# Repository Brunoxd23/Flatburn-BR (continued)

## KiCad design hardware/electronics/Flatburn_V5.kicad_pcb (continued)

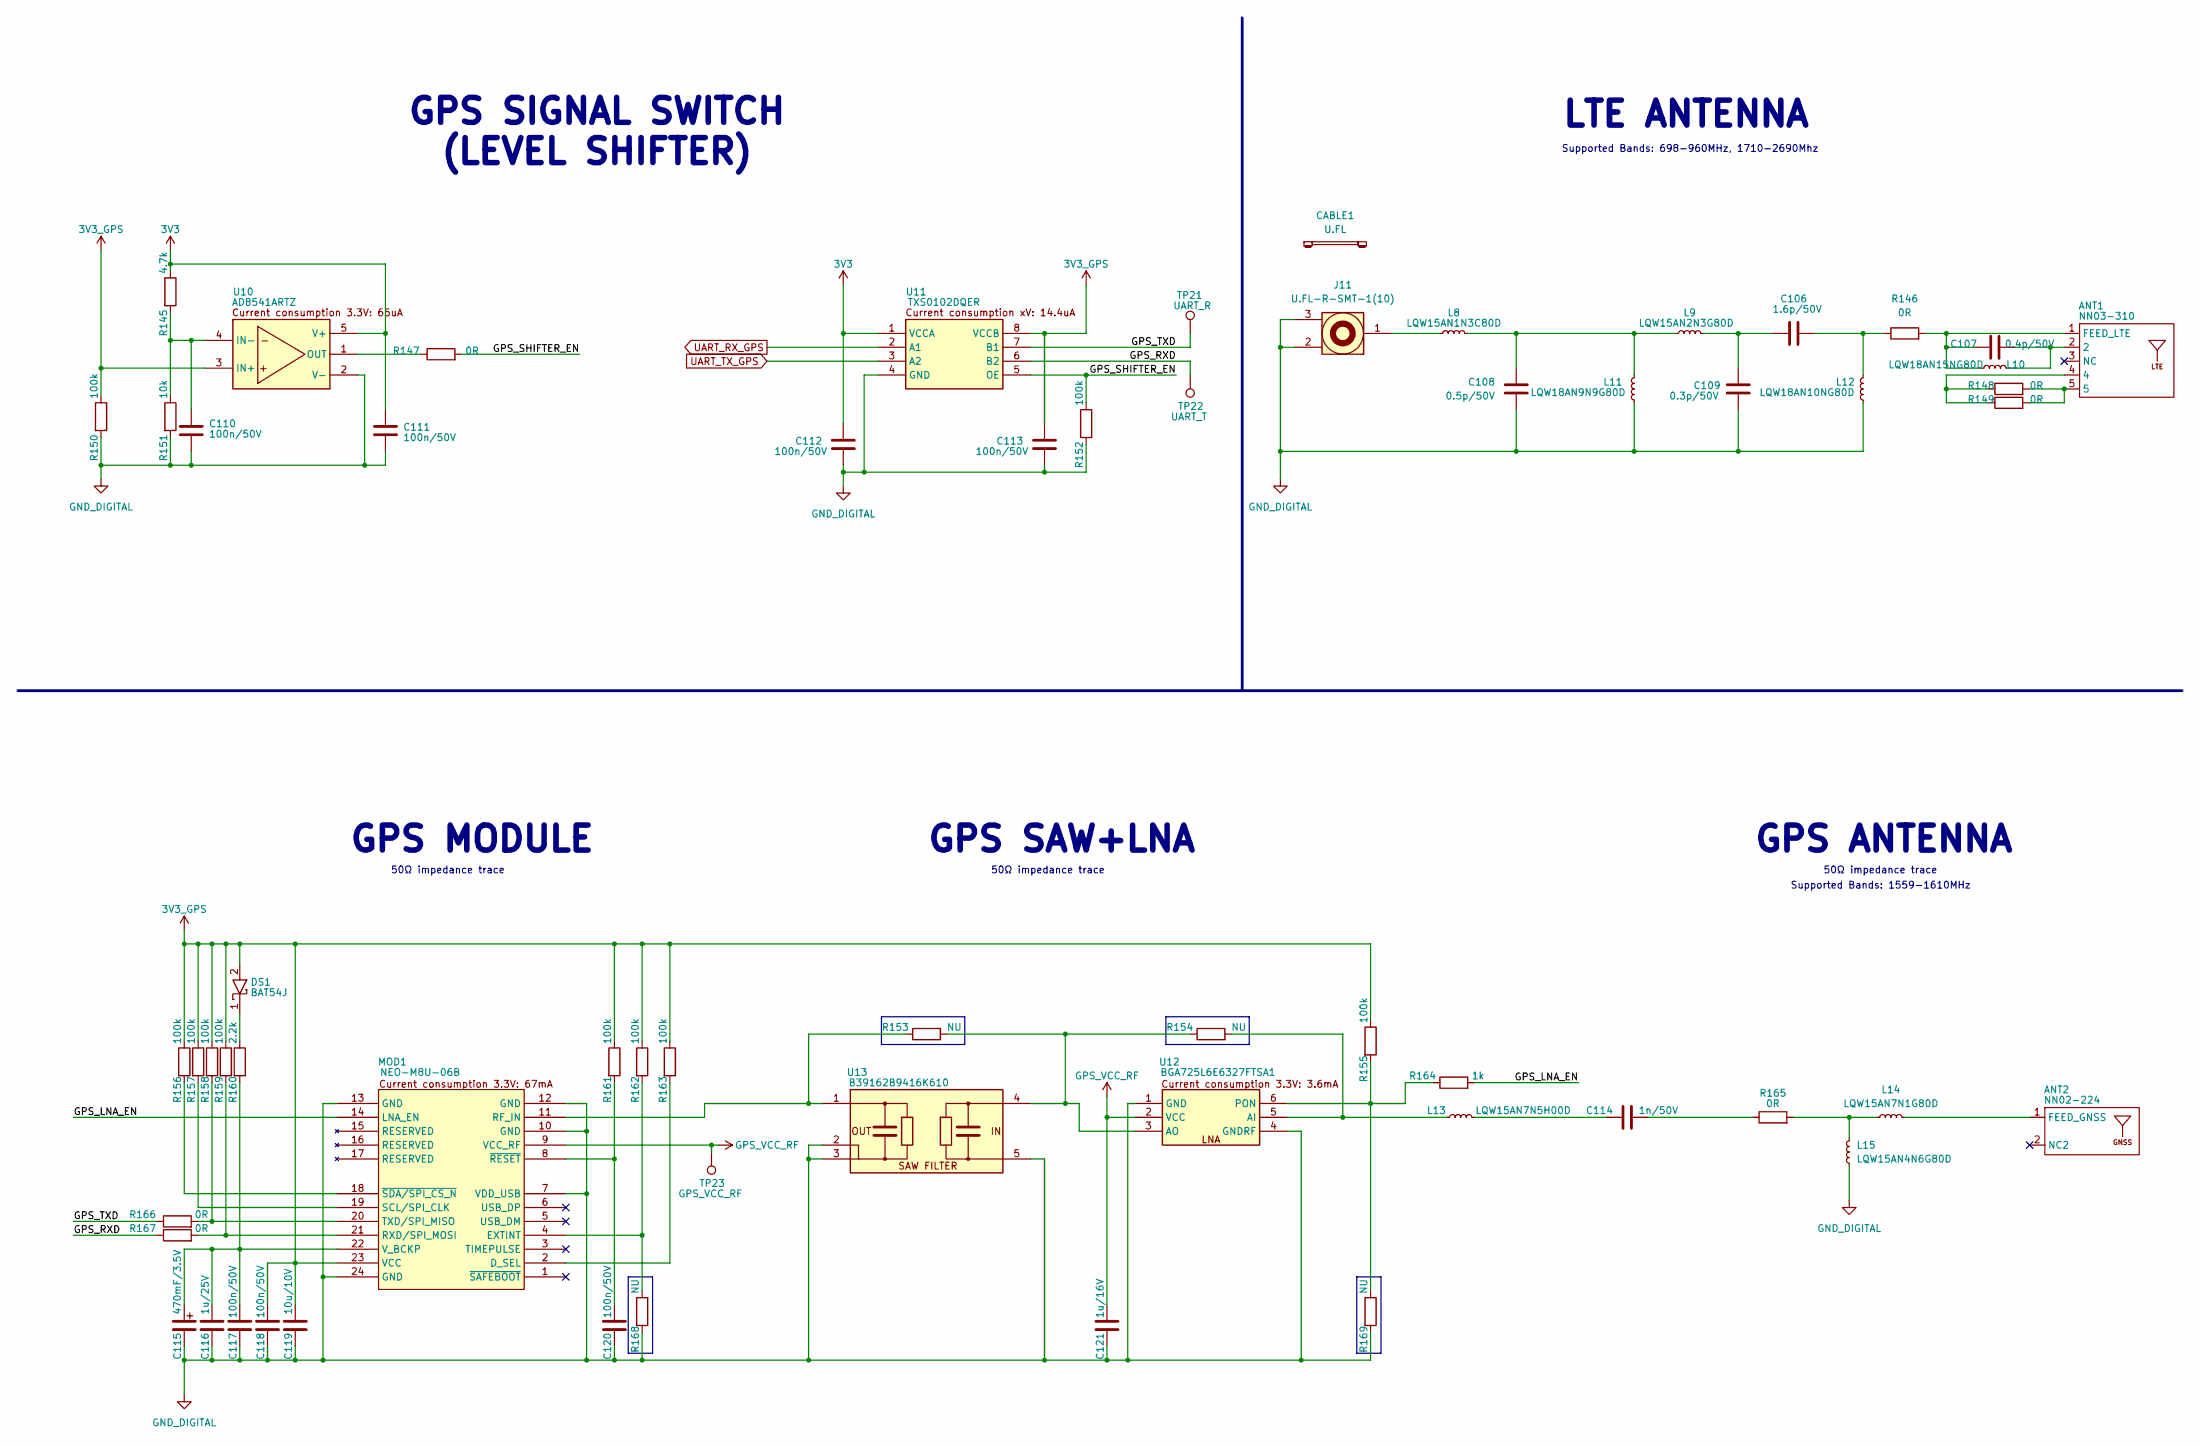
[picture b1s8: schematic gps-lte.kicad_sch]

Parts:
ANT1: NN03-310; XCVR_NN03-310; MPN NN03-310
ANT2: NN02-224; XCVR_NN02-224; MPN NN02-224
C106: 1.6p/50V; C_0402_1005Metric; MPN GJM1555C1H1R6WB01D
C107: 0.4p/50V; C_0402_1005Metric; MPN GJM1555C1HR40WB01D
C108: 0.5p/50V; C_0402_1005Metric; MPN GJM1555C1HR50WB01D
C109: 0.3p/50V; C_0402_1005Metric; MPN GJM1555C1HR30WB01D
C110, C111, C112, C113, C117, C118, C120: 100n/50V; C_0402_1005Metric
C114: 1n/50V; C_0402_1005Metric
C115: 470mF/3.5V; FCS0V474ZFTBR24_KEM; MPN FCS0V474ZFTBR24
C116: 1u/25V; C_0603_1608Metric; MPN CL10B105KA8NNNC
C119: 10u/10V; C_0603_1608Metric
C121: 1u/16V; C_0402_1005Metric; MPN GRM155C71C105KE11D
CABLE1: U.FL; MPN 2016493-1
DS1: BAT54J; D_SOD-323F; MPN BAT54J,115
J11: U.FL-R-SMT-1(10); MPN U.FL-R-SMT-1(10)
L8: LQW15AN1N3C80D; LQW15AN4N1G80D; MPN LQW15AN1N3C80D
L9: LQW15AN2N3G80D; MPN LQW15AN2N3G80D
L10: LQW18AN15NG80D; LQW18AN7N2G80D; MPN LQW18AN15NG80D
L11: LQW18AN9N9G80D; LQW18AN7N2G80D; MPN LQW18AN9N9G80D
L12: LQW18AN10NG80D; LQW18AN7N2G80D; MPN LQW18AN10NG80D
L13: LQW15AN7N5H00D; MPN LQW15AN7N5H00D
L14: LQW15AN7N1G80D; LQW15AN4N1G80D; MPN LQW15AN7N1G80D
L15: LQW15AN4N6G80D; LQW15AN4N1G80D; MPN LQW15AN4N6G80D
MOD1: NEO-M8U-06B; MOD24_NEO-M8U_UBL; MPN NEO-M8U-06B
R145: 4.7k; R_0402_1005Metric
R146, R148, R149, R165, R166, R167: 0R; R_0402_1005Metric; MPN MCS04020Z0000ZE000
R147: 0R; R_0402_1005Metric; MPN RCS04020000Z0ED
R150, R152, R155, R156, R157, R158, R159, R161, R162, R163: 100k; R_0402_1005Metric
R151: 10k; R_0402_1005Metric
R153, R154: NU; R_0402_1005Metric; MPN RCS04020000Z0ED
R160: 2.2k; R_0402_1005Metric
R164: 1k; R_0402_1005Metric
R168, R169: NU; R_0402_1005Metric
TP21: UART_R; TestPoint_Pad_D1.0mm
TP22: UART_T; TestPoint_Pad_D1.0mm
TP23: GPS_VCC_RF; TestPoint_Pad_D1.0mm
U10: AD8541ARTZ; SOT-23-5; MPN TXS0102DQER
U11: TXS0102DQER; SON35P100X140X40-8N; MPN TXS0102DQER
U12: BGA725L6E6327FTSA1; BGS12SN6E6327XTSA1; MPN BGA725L6E6327FTSA1
U13: B39162B9416K610; MPN B39162B9416K610

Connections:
3V3: C111.1, C112.1, R145.1, U10.5 (V+), U11.1 (VCCA); also elsewhere on the board
3V3_GPS: C113.1, C118.1, C119.1, DS1.2, MOD1.23 (VCC), R150.1, R155.1, R156.1, R157.1, R158.1, R159.1, R161.1, R162.1, R163.1, U10.3 (IN+), U11.8 (VCCB); also elsewhere on the board
/06 - GPS-LTE/GPS_LNA_EN: MOD1.14 (LNA_EN), R164.2
/06 - GPS-LTE/GPS_RXD: R167.1, TP22.1, U11.6 (B2)
/06 - GPS-LTE/GPS_SHIFTER_EN: R147.2, R152.1, U11.5 (OE)
/06 - GPS-LTE/GPS_TXD: R166.1, TP21.1, U11.7 (B1)
GND_DIGITAL: C108.2, C109.2, C110.2, C111.2, C112.2, C113.2, C115.2 (-), C116.2, C117.2, C118.2, C119.2, C120.2, C121.2, J11.2, J11.3, L11.2, L12.2, L15.2, MOD1.7 (VDD_USB), MOD1.10 (GND), MOD1.12 (GND), MOD1.13 (GND), MOD1.24 (GND), R150.2, R151.2, R152.2, R168.2, R169.2, U10.2 (V-), U11.4 (GND), U12.1 (GND), U12.4 (GNDRF), U13.2 (GND1), U13.3 (GND2), U13.5 (GND3); also elsewhere on the board
GPS_VCC_RF: C121.1, MOD1.9 (VCC_RF), TP23.1, U12.2 (VCC)
unnamed: ANT1.1 (FEED_LTE), C107.1, L10.2, R146.2
unnamed: ANT1.2, C107.2, L10.1
unnamed: ANT1.4, R148.1, R149.1
unnamed: ANT1.5, R148.2, R149.2
unnamed: ANT2.1 (FEED_GNSS), L14.1
unnamed: C106.1, C109.1, L9.1
unnamed: C106.2, L12.1, R146.1
unnamed: C108.1, L8.1, L9.2, L11.1
unnamed: C114.1, L13.1
unnamed: C114.2, R165.1
unnamed: C115.1 (+), C116.1, C117.1, MOD1.22 (V_BCKP), R160.2
unnamed: DS1.1, R160.1
unnamed: J11.1, L8.2
unnamed: L14.2, L15.1, R165.2
unnamed: MOD1.2 (D_SEL), R163.2
unnamed: MOD1.4 (EXTINT), R162.2, R168.1
unnamed: MOD1.11 (RF_IN), R153.1, U13.1 (OUT)
unnamed: MOD1.21 (RXD/SPI_MOSI), R159.2, R167.2
unnamed: MOD1.19 (SCL/SPI_CLK), R157.2
unnamed: MOD1.20 (TXD/SPI_MISO), R158.2, R166.2
unnamed: C120.1, MOD1.8 (~RESET), R161.2
unnamed: MOD1.18 (~SDA/SPI_CS_N), R156.2
unnamed: C110.1, R145.2, R151.1, U10.4 (IN-)
unnamed: R147.1, U10.1 (OUT)
unnamed: L13.2, R154.2, U12.5 (AI)
unnamed: R153.2, R154.1, U12.3 (AO), U13.4 (IN)
unnamed: R155.2, R164.1, R169.1, U12.6 (PON)
UART_RX_GPS: U11.2 (A1); also elsewhere on the board
UART_TX_GPS: U11.3 (A2); also elsewhere on the board

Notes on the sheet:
GPS SIGNAL SWITCH (LEVEL SHIFTER)
GPS SAW+LNA
GPS ANTENNA
50Ω impedance trace
LTE ANTENNA
GPS MODULE
Supported Bands: 698-960MHz, 1710-2690Mhz
Supported Bands: 1559-1610MHz

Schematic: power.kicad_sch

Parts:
C5, C6, C14: 10n/50V; C_0402_1005Metric
C7: 4.7u/35V; C_0603_1608Metric
C8, C11: 10u/10V; C_0603_1608Metric
C9, C10: 330p/10V; C_0402_1005Metric; MPN C0402C331K8RACTU
C12, C21: 4.7u/10V; C_0603_1608Metric
C13: 47u/50V; CP_Elec_8x10; MPN GXC1H470MCQ1GS
C15, C16: 47n/25V; C_0402_1005Metric
C17, C18, C24, C25, C26: 10u/50V; C_0805_2012Metric; MPN GRM21BR61H106KE43L
C19, C27, C33: 100n/50V; C_0402_1005Metric
C20: 1n/50V; C_0402_1005Metric
C22, C23: 10u/25V; C_0603_1608Metric
C28, C29, C30, C31, C32: 10u/25V; C_0603_1608Metric; MPN GRM188R61E106KA73D
DZ2, DZ3: BZT52C12T-7; D_SOD-523; MPN BZT52C12T-7
J8: STRIP-2P-M; PinHeader_1x02_P2.54mm_Vertical
L3: SPM6550T-1R0M100A; SPM6550; MPN SPM6550T-1R0M100A
LD1: IN-S63ASR; INS63ASR; MPN IN-S63ASR
PB1: 1571634-2; 15716342; MPN 1571634-2
Q2, Q3, Q4, Q5: SISH402DN-T1-GE3; PowerPAK 121-8; MPN SISH402DN-T1-GE3
Q6: BSS84WQ-7-F; SOT-323_SC-70; MPN BSS84WQ-7-F
R5: NU; R_1206_3216Metric; MPN RCA12060000ZSEA
R6, R7, R9, R11, R13, R15, R17, R18, R19, R24, R29, R33: 10k; R_0402_1005Metric
R8, R10, R12, R14, R16: NU; R_0402_1005Metric
R20, R25: 264R; R_0603_1608Metric; MPN CRCW0603294RFKEA
R21: 255k; R_0402_1005Metric; MPN RC0402FR-07255KL
R22: 100k; R_0402_1005Metric
R23: 560R; R_0402_1005Metric
R26: NU; R_0603_1608Metric; MPN RCA06030000ZSEA
R27: NU; R_0402_1005Metric; MPN RCS04020000Z0ED
R28, R31: 100R; R_0402_1005Metric
R30: 5.23k; R_0402_1005Metric
R32: 30.1k; R_0402_1005Metric
R34: NU; R_0603_1608Metric
R35: 3k; R_0603_1608Metric
TP1: TestPoint; TestPoint_Pad_D1.0mm
TP2: CAP_MIS; TestPoint_Pad_D1.0mm
TP3: n_SINK_EN; TestPoint_Pad_D1.0mm
TP4: VSOLAR; TestPoint_Pad_D1.0mm
TP5: VSYS; TestPoint_Pad_D1.0mm
TP6: VBUS; TestPoint_Pad_D1.0mm
TP7: BC_LDO; TestPoint_Pad_D1.0mm
TP8: VUSB_PD; TestPoint_Pad_D1.0mm
TP9: VBAT; TestPoint_Pad_D1.0mm
TP10: GND; TestPoint_Pad_D1.0mm
TP37: n_FAULT_IN; TestPoint_Pad_D1.0mm
TVS19: D5V0S1U2LP-7B; D5V0S1U2LP7B; MPN M-621-D5V0S1U2LP-7B
U1: TPS25730DREFR; MPN TPS25730DREFR
U2: BQ25798RQMR; MPN BQ25798RQMR

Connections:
/03 - POWER/ADCIN1: R8.1, R13.2, U1.2 (ADCIN1)
/03 - POWER/ADCIN2: R9.1, R14.2, U1.3 (ADCIN2)
/03 - POWER/ADCIN3: R10.1, R15.2, U1.5 (ADCIN3)
/03 - POWER/ADCIN4: R11.1, R16.2, U1.7 (ADCIN4)
/03 - POWER/ILIM_HIZ: R21.2, R22.1, U2.17 (ILIM_HIZ)
/03 - POWER/REGN: C21.1, R21.1, R23.1, R24.1, R29.1, R30.1, TP7.1, U2.5 (REGN)
/03 - POWER/STAT: Q6.1 (G), R24.2, R27.1, U2.1 (STAT)
/03 - POWER/TS: J8.1, R30.2, R32.1, R33.1, U2.16 (TS)
/03 - POWER/VUSB_PD: C13.1, C14.1, Q4.5 (D), Q4.6 (D), Q4.7 (D), Q4.8 (D), Q4.9 (D), R5.2, TP1.1, TP8.1, U1.20 (PPHV_1), U1.21 (PPHV_2), U1.22 (PPHV_3), U1.41 (PPHV_4), U2.8 (VAC2)
CC1: C9.1, U1.28 (CC1); also elsewhere on the board
CC2: C10.1, U1.29 (CC2); also elsewhere on the board
GND_DIGITAL: C5.2, C6.2, C7.2, C8.2, C9.2, C10.2, C11.2, C12.2, C13.2, C14.2, C17.2, C18.2, C19.2, C20.2, C21.2, C22.2, C23.2, C24.2, C25.2, C26.2, C27.2, C28.2, C29.2, C30.2, C31.2, C32.2, C33.2, J8.2, PB1.3, PB1.4, Q6.3 (D), R13.1, R14.1, R15.1, R16.1, R17.2, R18.2, R19.2, R22.2, R32.2, R33.2, R34.2, R35.2, TP10.1, TVS19.2, U1.11 (GND_1), U1.12 (GND_2), U1.14 (GND_3), U1.16 (GND_4), U1.17 (GND_5), U1.31 (GND_6), U1.34 (GND_7), U1.35 (GND_8), U1.39 (GND_9), U1.44 (GND_10), U2.13 (~CE), U2.27 (GND); also elsewhere on the board
I2C_SCL: U1.9 (I2CT_SCL), U2.14 (SCL); also elsewhere on the board
I2C_SDA: U1.8 (I2CT_SDA), U2.15 (SDA); also elsewhere on the board
LDO_3V3: C11.1, R6.1, R7.1, R8.2, R9.2, R10.2, R11.2, R12.1, U1.1 (LDO_3V3)
unnamed: DZ2.2, Q2.1 (S), Q2.2 (S), Q2.3 (S), Q3.1 (S), Q3.2 (S), Q3.3 (S)
unnamed: DZ3.2, Q4.1 (S), Q4.2 (S), Q4.3 (S), Q5.1 (S), Q5.2 (S), Q5.3 (S)
unnamed: LD1.2 (A), R23.2
unnamed: LD1.1 (K), Q6.2 (S), R27.2
unnamed: PB1.1, PB1.2, R31.1, TVS19.1
unnamed: DZ2.1, Q2.4 (G), Q3.4 (G), R20.1
unnamed: DZ3.1, Q4.4 (G), Q5.4 (G), R25.1
unnamed: R6.2, TP2.1, U1.6 (CAP_MIS)
unnamed: U1.15 (DRAIN_1), U1.30 (DRAIN_2), U1.40 (DRAIN_3)
unnamed: C12.1, U1.4 (LDO_1V5)
unnamed: R19.1, U1.26 (RESERVED_1)
unnamed: R18.1, U1.27 (RESERVED_2)
unnamed: R17.1, U1.36 (RESERVED_3)
unnamed: C8.1, U1.38 (VIN_3V3)
unnamed: R7.2, TP37.1, U1.18 (~FAULT_IN)
unnamed: R20.2, U2.11 (ACDRV1)
unnamed: R25.2, U2.10 (ACDRV2)
unnamed: R28.1, U2.18 (BATP)
unnamed: C15.1, U2.4 (BTST1)
unnamed: C16.2, U2.19 (BTST2)
unnamed: C24.1, C25.1, C26.1, C27.1, U2.29 (PMID)
unnamed: R34.1, R35.1, U2.20 (PROG)
unnamed: C20.1, U2.24 (SDRV)
unnamed: C15.2, L3.1, U2.28 (SW1)
unnamed: C16.1, L3.2, U2.26 (SW2)
unnamed: R29.2, U2.21 (~INT)
unnamed: R31.2, U2.12 (~QON)
VBAT: C22.1, C23.1, R26.1, R28.2, TP9.1, U2.22 (BAT), U2.23 (BAT); also elsewhere on the board
VBUS: Q3.5 (D), Q3.6 (D), Q3.7 (D), Q3.8 (D), Q3.9 (D), Q5.5 (D), Q5.6 (D), Q5.7 (D), Q5.8 (D), Q5.9 (D); also elsewhere on the board
VBUS_CURSEN: C17.1, C18.1, C19.1, TP6.1, U2.2 (VBUS), U2.3 (VBUS); also elsewhere on the board
VSOLAR: Q2.5 (D), Q2.6 (D), Q2.7 (D), Q2.8 (D), Q2.9 (D), TP4.1, U2.9 (VAC1); also elsewhere on the board
VSYS: C28.1, C29.1, C30.1, C31.1, C32.1, C33.1, R26.2, TP5.1, U2.25 (SYS); also elsewhere on the board
VUSB: C5.1, C6.1, C7.1, R5.1, U1.23 (VBUS_IN_1), U1.24 (VBUS_IN_2), U1.25 (VBUS_IN_3), U1.32 (VBUS_1), U1.33 (VBUS_2), U1.42 (VBUS_IN_4), U1.43 (VBUS_3); also elsewhere on the board
nUSB_SINK_EN: R12.2, TP3.1, U1.19 (~SINK_EN); also elsewhere on the board

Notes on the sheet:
ADCINx pins Configure Default Behavior,read Datasheet for more info In this version: 5V min 20V max 0,5A min 5A max I2C Address: 0x20
CURRENT SENSE VBUS
PROG pin sets default Switching Frequency and Battery Cell Count In this version: f:1.5MHz Cell:1S
I2C Address: 0x6B
Bypass U1
External battery thermistor connector If thermistor is mounted, remove R33 10K resistor
BATTERY CHARGER
Battery charger reset 10s press
VSYSMax 1S Battery = 4.55V VSYSMax 2S Battery = 8.77V
Input current limit Set to 500mA To increase change IINDPM register value
LED ON = Charging in progress LED BLINK = Fault condition LED OFF = Charging completed/disabled
I2C Address: 0x20
USB PD CONTROLLER

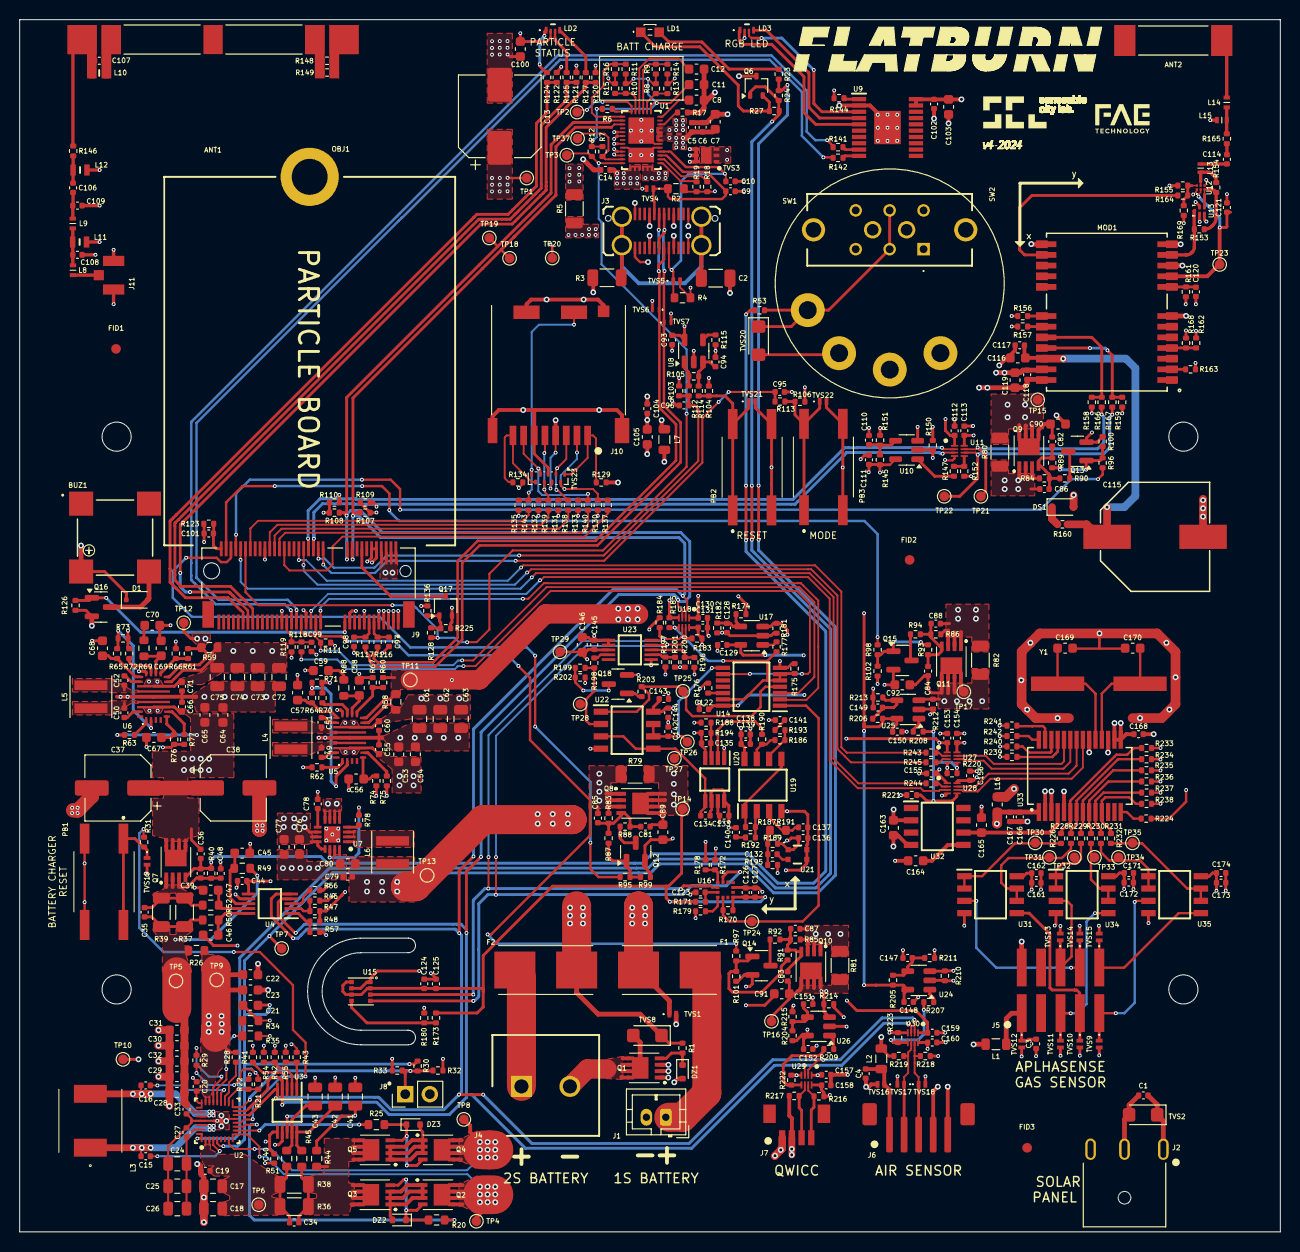
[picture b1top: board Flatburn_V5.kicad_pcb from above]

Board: 4 copper layers, 130.0 x 125.0 mm, 586 parts (0 on the bottom side), 290 nets.

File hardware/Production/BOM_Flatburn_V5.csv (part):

Item,Reference,Value,MPN,Description,Distributor,Pkg Type,Footprint,Notes
1,ANT1,NN03-310,NN03-310,"Ignion TRIO mXTENDT (NN03-310),GSM, UMTS, LTE, LTE-M, NB-IoT, 5G, GNSS, Bluetooth, 400-8000MHz, 30X3X1mm",M-128-NN03-310 ,SMD,FAE-ANT:XCVR_NN03-310,
2,ANT2,NN02-224,NN02-224 ,"Ignion RUN mXTENDâ„¢ (NN02-224) GNSS antenna, 824-8000 MHz",M-128-NN02-224 ,SMD,FAE-ANT:XCVR_NN02-224,
3,BUZ1,ST-025BH,ST-025BH,"BUZZER MAGN 3V 7.5X7.5 SMD, 2,7KHz, 8RdBA",D-433-1087-2-ND,SMD,FAE-BUZZ:ST-025BH_SOB,
4,C1,100n/50V,,CHIP CAP.CER. 100nF 50V 10% X7R 0402,FAE-043362,SMD,Capacitor_SMD:C_0402_1005Metric,
5,C2,10n/1kV,,CHIP CAP.CER. 10nF 1kV 10% X7R 1206,FAE-028470,SMD,Capacitor_SMD:C_1206_3216Metric,
6,C3,100n/50V,,CHIP CAP.CER. 100nF 50V 10% X7R 0402,FAE-043362,SMD,Capacitor_SMD:C_0402_1005Metric,
7,C4,100n/50V,,CHIP CAP.CER. 100nF 50V 10% X7R 0402,FAE-043362,SMD,Capacitor_SMD:C_0402_1005Metric,
8,C5,10n/50V,,CHIP CAP.CER. 10nF 50V 10% X7R 0402,FAE-101362,SMD,Capacitor_SMD:C_0402_1005Metric,
9,C6,10n/50V,,CHIP CAP.CER. 10nF 50V 10% X7R 0402,FAE-101362,SMD,Capacitor_SMD:C_0402_1005Metric,
10,C7,4.7u/35V,,CHIP CAP.CER. 4.7u 35V 10% X5R 0603,FAE-057733,SMD,Capacitor_SMD:C_0603_1608Metric,
11,C8,10u/10V,,CHIP CAP.CER. 10u 10V 10% X5R 0603,FAE-028168,SMD,Capacitor_SMD:C_0603_1608Metric,
12,C9,330p/10V,C0402C331K8RACTU,CHIP CAP.CER. 330p 10V 10% X7R 0402,M-80-C0402C331K8R ,SMD,Capacitor_SMD:C_0402_1005Metric,
13,C10,330p/10V,C0402C331K8RACTU,CHIP CAP.CER. 330p 10V 10% X7R 0402,M-80-C0402C331K8R ,SMD,Capacitor_SMD:C_0402_1005Metric,
14,C11,10u/10V,,CHIP CAP.CER. 10u 10V 10% X5R 0603,FAE-028168,SMD,Capacitor_SMD:C_0603_1608Metric,
15,C12,4.7u/10V,,CHIP CAP.CER. 4.7u 10V 10% X5R 0603,FAE-033362,SMD,Capacitor_SMD:C_0603_1608Metric,
16,C13,47u/50V,GXC1H470MCQ1GS,AL ORG POLR. 47u 50V 20% 8X10,M-647-GXC1H470MCQ1GS ,SMD,Capacitor_SMD:CP_Elec_8x10,
17,C14,10n/50V,,CHIP CAP.CER. 10nF 50V 10% X7R 0402,FAE-101362,SMD,Capacitor_SMD:C_0402_1005Metric,
18,C15,47n/25V,,CHIP CAP.CER. 47nF 25V 10% X7R 0402,FAE-029703,SMD,Capacitor_SMD:C_0402_1005Metric,
19,C16,47n/25V,,CHIP CAP.CER. 47nF 25V 10% X7R 0402,FAE-029703,SMD,Capacitor_SMD:C_0402_1005Metric,
20,C17,10u/50V,GRM21BR61H106KE43L,CHIP CAP.CER. 10u 50V 10% X5R 0805,M-81-GRM21BR61H106KE3L ,SMD,Capacitor_SMD:C_0805_2012Metric,
21,C18,10u/50V,GRM21BR61H106KE43L,CHIP CAP.CER. 10u 50V 10% X5R 0805,M-81-GRM21BR61H106KE3L ,SMD,Capacitor_SMD:C_0805_2012Metric,
22,C19,100n/50V,,CHIP CAP.CER. 100nF 50V 10% X7R 0402,FAE-043362,SMD,Capacitor_SMD:C_0402_1005Metric,
23,C20,1n/50V,,CHIP CAP.CER. 1nF 50V 10% X7R 0402,FAE-043572,SMD,Capacitor_SMD:C_0402_1005Metric,
24,C21,4.7u/10V,,CHIP CAP.CER. 4.7u 10V 10% X5R 0603,FAE-033362,SMD,Capacitor_SMD:C_0603_1608Metric,
25,C22,10u/25V,,CHIP CAP.CER. 10u 25V 20% X5R 0603,FAE-055937,SMD,Capacitor_SMD:C_0603_1608Metric,
26,C23,10u/25V,,CHIP CAP.CER. 10u 25V 20% X5R 0603,FAE-055937,SMD,Capacitor_SMD:C_0603_1608Metric,
27,C24,10u/50V,GRM21BR61H106KE43L,CHIP CAP.CER. 10u 50V 10% X5R 0805,M-81-GRM21BR61H106KE3L ,SMD,Capacitor_SMD:C_0805_2012Metric,
28,C25,10u/50V,GRM21BR61H106KE43L,CHIP CAP.CER. 10u 50V 10% X5R 0805,M-81-GRM21BR61H106KE3L ,SMD,Capacitor_SMD:C_0805_2012Metric,
29,C26,10u/50V,GRM21BR61H106KE43L,CHIP CAP.CER. 10u 50V 10% X5R 0805,M-81-GRM21BR61H106KE3L ,SMD,Capacitor_SMD:C_0805_2012Metric,
30,C27,100n/50V,,CHIP CAP.CER. 100nF 50V 10% X7R 0402,FAE-043362,SMD,Capacitor_SMD:C_0402_1005Metric,
31,C28,10u/25V,GRM188R61E106KA73D,CHIP CAP.CER. 10u 25V 10% X5R 0603,M-81-GRM188R61E106KA3D ,SMD,Capacitor_SMD:C_0603_1608Metric,
32,C29,10u/25V,GRM188R61E106KA73D,CHIP CAP.CER. 10u 25V 10% X5R 0603,M-81-GRM188R61E106KA3D ,SMD,Capacitor_SMD:C_0603_1608Metric,
33,C30,10u/25V,GRM188R61E106KA73D,CHIP CAP.CER. 10u 25V 10% X5R 0603,M-81-GRM188R61E106KA3D ,SMD,Capacitor_SMD:C_0603_1608Metric,
34,C31,10u/25V,GRM188R61E106KA73D,CHIP CAP.CER. 10u 25V 10% X5R 0603,M-81-GRM188R61E106KA3D ,SMD,Capacitor_SMD:C_0603_1608Metric,
35,C32,10u/25V,GRM188R61E106KA73D,CHIP CAP.CER. 10u 25V 10% X5R 0603,M-81-GRM188R61E106KA3D ,SMD,Capacitor_SMD:C_0603_1608Metric,
36,C33,100n/50V,,CHIP CAP.CER. 100nF 50V 10% X7R 0402,FAE-043362,SMD,Capacitor_SMD:C_0402_1005Metric,
37,C34,100n/50V,,CHIP CAP.CER. 100nF 50V 10% X7R 0402,FAE-043362,SMD,Capacitor_SMD:C_0402_1005Metric,
38,C35,100n/50V,,CHIP CAP.CER. 100nF 50V 10% X7R 0402,FAE-043362,SMD,Capacitor_SMD:C_0402_1005Metric,
39,C36,10p/50V,GCM1555C1H100JA16D,CHIP CAP.CER. 10p 50V 5% C0G 0402,FAE-043366,SMD,Capacitor_SMD:C_0402_1005Metric,
40,C37,220u/25V,UCM1E221MCL1GS,"EL POLR. 220u 25V 20% 6,3x7,7",M-647-UCM1E221MCL1GS ,SMD,Capacitor_SMD:CP_Elec_6.3x7.7,
41,C38,220u/25V,UCM1E221MCL1GS,"EL POLR. 220u 25V 20% 6,3x7,7",M-647-UCM1E221MCL1GS ,SMD,Capacitor_SMD:CP_Elec_6.3x7.7,
42,C39,NU,,CHIP CAP.CER. 100nF 50V 10% X7R 0402,FAE-043362,SMD,Capacitor_SMD:C_0402_1005Metric,NOT MOUNTED
43,C40,100n/50V,,CHIP CAP.CER. 100nF 50V 10% X7R 0402,FAE-043362,SMD,Capacitor_SMD:C_0402_1005Metric,
44,C41,1u/50V,,CHIP CAP.CER. 1u 50V 10% X7R 0805,FAE-027166,SMD,Capacitor_SMD:C_0805_2012Metric,
45,C42,1u/50V,,CHIP CAP.CER. 1u 50V 10% X7R 0805,FAE-027166,SMD,Capacitor_SMD:C_0805_2012Metric,
46,C43,1u/50V,,CHIP CAP.CER. 1u 50V 10% X7R 0805,FAE-027166,SMD,Capacitor_SMD:C_0805_2012Metric,
47,C44,100n/50V,,CHIP CAP.CER. 100nF 50V 10% X7R 0402,FAE-043362,SMD,Capacitor_SMD:C_0402_1005Metric,
48,C45,1u/25V,CL10B105KA8NNNC,CHIP CAP.CER. 1u 25V 10% X7R 0603,FAE-100573,SMD,Capacitor_SMD:C_0603_1608Metric,
49,C46,1u/25V,CL10B105KA8NNNC,CHIP CAP.CER. 1u 25V 10% X7R 0603,FAE-100573,SMD,Capacitor_SMD:C_0603_1608Metric,
50,C47,1u/25V,CL10B105KA8NNNC,CHIP CAP.CER. 1u 25V 10% X7R 0603,FAE-100573,SMD,Capacitor_SMD:C_0603_1608Metric,
51,C48,NU,,CHIP CAP.CER. 100nF 50V 10% X7R 0402,FAE-043362,SMD,Capacitor_SMD:C_0402_1005Metric,NOT MOUNTED
52,C49,100n/50V,,CHIP CAP.CER. 100nF 50V 10% X7R 0402,FAE-043362,SMD,Capacitor_SMD:C_0402_1005Metric,
53,C50,100n/50V,,CHIP CAP.CER. 100nF 50V 10% X7R 0402,FAE-043362,SMD,Capacitor_SMD:C_0402_1005Metric,
54,C51,100n/50V,,CHIP CAP.CER. 100nF 50V 10% X7R 0402,FAE-043362,SMD,Capacitor_SMD:C_0402_1005Metric,
55,C52,100n/50V,,CHIP CAP.CER. 100nF 50V 10% X7R 0402,FAE-043362,SMD,Capacitor_SMD:C_0402_1005Metric,
56,C53,10u/25V,GRM188R61E106KA73D,CHIP CAP.CER. 10u 25V 10% X5R 0603,M-81-GRM188R61E106KA3D ,SMD,Capacitor_SMD:C_0603_1608Metric,
57,C54,10u/25V,GRM188R61E106KA73D,CHIP CAP.CER. 10u 25V 10% X5R 0603,M-81-GRM188R61E106KA3D ,SMD,Capacitor_SMD:C_0603_1608Metric,
58,C55,100n/50V,,CHIP CAP.CER. 100nF 50V 10% X7R 0402,FAE-043362,SMD,Capacitor_SMD:C_0402_1005Metric,
59,C56,NU,GRM188R61E106KA73D,CHIP CAP.CER. 10u 25V 10% X5R 0603,M-81-GRM188R61E106KA3D ,SMD,Capacitor_SMD:C_0603_1608Metric,NOT MOUNTED
60,C57,10u/25V,GRM188R61E106KA73D,CHIP CAP.CER. 10u 25V 10% X5R 0603,M-81-GRM188R61E106KA3D ,SMD,Capacitor_SMD:C_0603_1608Metric,
61,C58,330p/25V,C0603C331J3HACAUTO ,CHIP CAP.CER. 330p 25V 5% X8R 0603,M-80-C0603C331J3HAUTO ,SMD,Capacitor_SMD:C_0603_1608Metric,
62,C59,22n/16V,0603YC223J4T2A ,CHIP CAP.CER. 22n 16V 5% X7R 0603,M-581-0603YC223J4T2A ,SMD,Capacitor_SMD:C_0603_1608Metric,
63,C60,100n/50V,,CHIP CAP.CER. 100nF 50V 10% X7R 0402,FAE-043362,SMD,Capacitor_SMD:C_0402_1005Metric,
64,C61,22u/16V,GRM21BC81C226ME44L,CHIP CAP.CER. 22u 16V 20% X6S 0805,M-81-GRM21BC81C226ME4L ,SMD,Capacitor_SMD:C_0805_2012Metric,
65,C62,22u/16V,GRM21BC81C226ME44L,CHIP CAP.CER. 22u 16V 20% X6S 0805,M-81-GRM21BC81C226ME4L ,SMD,Capacitor_SMD:C_0805_2012Metric,
66,C63,22u/16V,GRM21BC81C226ME44L,CHIP CAP.CER. 22u 16V 20% X6S 0805,M-81-GRM21BC81C226ME4L ,SMD,Capacitor_SMD:C_0805_2012Metric,
67,C64,10u/25V,GRM188R61E106KA73D,CHIP CAP.CER. 10u 25V 10% X5R 0603,M-81-GRM188R61E106KA3D ,SMD,Capacitor_SMD:C_0603_1608Metric,
68,C65,10u/25V,GRM188R61E106KA73D,CHIP CAP.CER. 10u 25V 10% X5R 0603,M-81-GRM188R61E106KA3D ,SMD,Capacitor_SMD:C_0603_1608Metric,
69,C66,100n/50V,,CHIP CAP.CER. 100nF 50V 10% X7R 0402,FAE-043362,SMD,Capacitor_SMD:C_0402_1005Metric,
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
